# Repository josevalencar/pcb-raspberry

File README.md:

# Projeto de Placa de Circuito Impresso com Raspberry Pi Pico W - José Vitor Alencar

## Descrição
Este repositório contém os arquivos e recursos necessários para a construção de uma placa de circuito impresso (PCB) projetada para acoplar um Raspberry Pi Pico W. A placa inclui um dispositivo de acionamento de potência (transistor neste caso), um dispositivo sinalizador (LED neste caso) e um dispositivo de entrada (analógico ou digital). 

## Componentes
- **Raspberry Pi Pico W:** Responsável pelo controle e processamento.
- **Transistor:** Utilizado para o acionamento de cargas ou dispositivos externos.
- **LED:** Serve como dispositivo de sinalização para o usuário.

## Estrutura do Repositório

```
/
├── circuito
│   ├── circuito-backups
│   ├── gerber-files # Arquivos gerber para fabricação
│   └── circuito.kicad # Arquivos kicad do circuito
├── src
│   └── teste.py  # Script principal para testar a pcb com o Raspberry Pi Pico W
└── README.md
```

## Imagens
### Esquemático no KiCad

*Figura 1: Esquemático do projeto desenvolvido no KiCad.*

### Editor de PCI no KiCad

*Figura 2: Layout da placa no editor de PCI do KiCad.*

### Visualizador 3D no KiCad

*Figura 3: Layout da placa com visualização 3D.*

## Como Usar
O diretório `circuito` contém os arquivos para o kicad. O diretório `src` tem um arquivo teste em python.

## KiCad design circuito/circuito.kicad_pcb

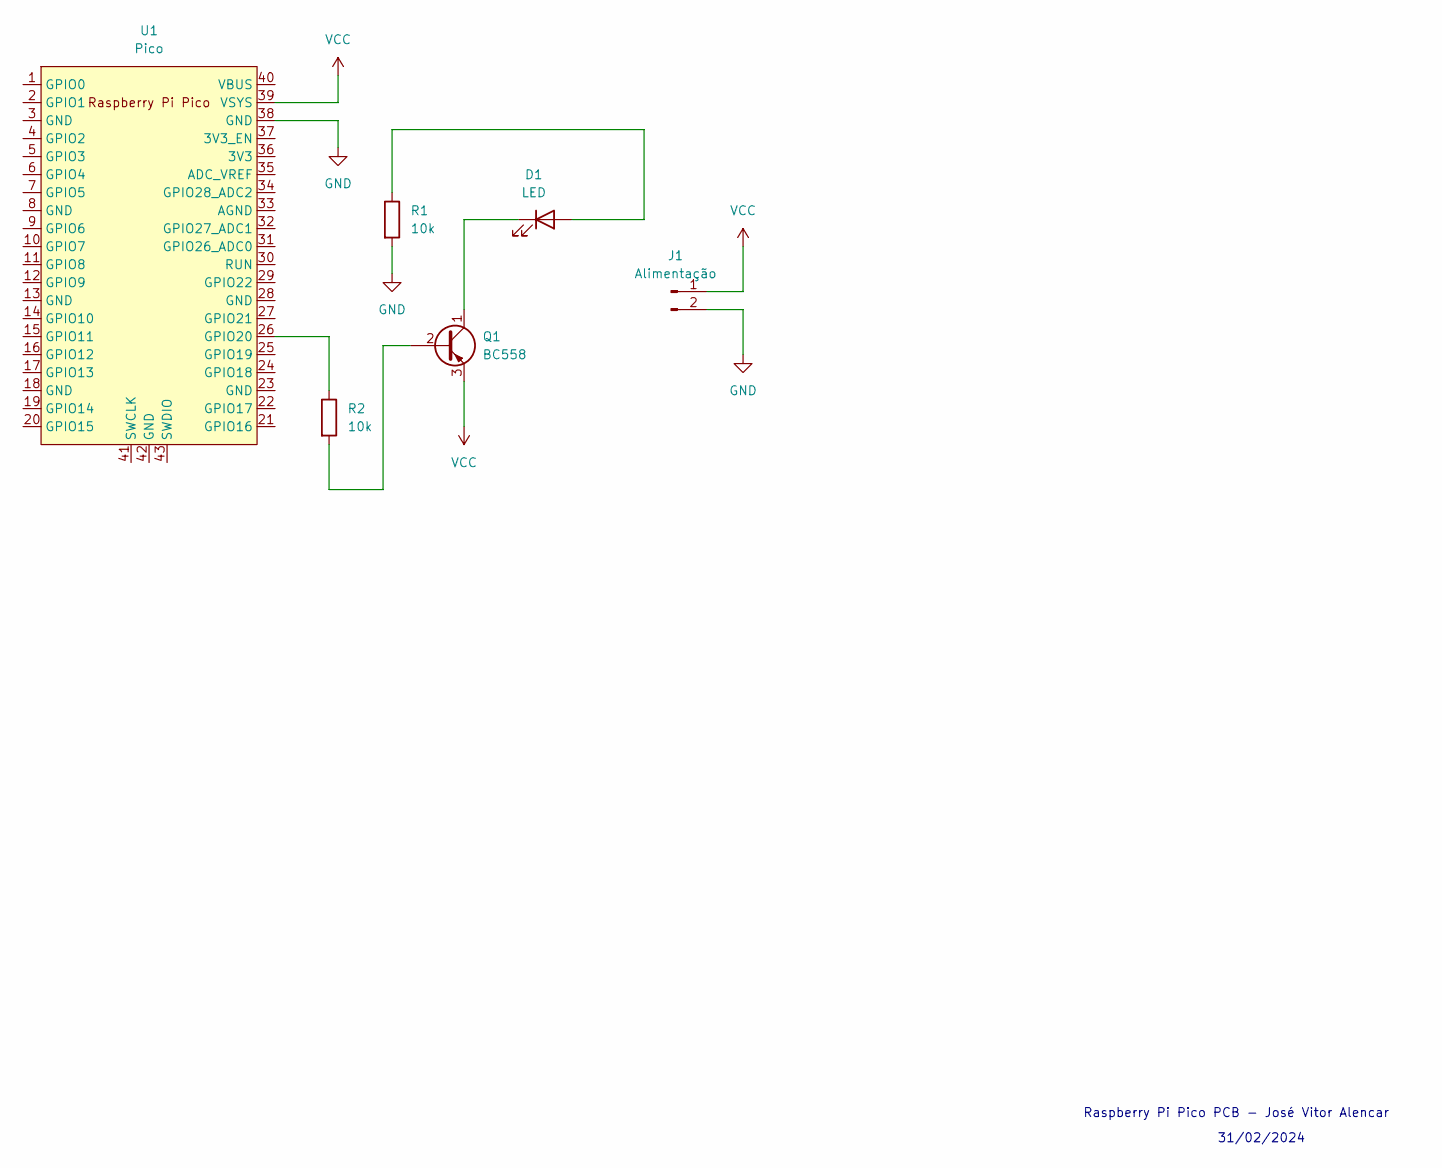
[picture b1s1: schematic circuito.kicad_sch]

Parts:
D1: LED; LED_0201_0603Metric
J1: Alimentação; AMASS_XT30PW-F_1x02_P2.50mm_Horizontal
Q1: BC558; TO-92_Inline
R1, R2: 10k; R_LDR_4.9x4.2mm_P2.54mm_Vertical
U1: Pico; RPi_Pico_SMD_TH

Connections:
GND: J1.2, R1.2, U1.38 (GND)
unnamed: D1.2 (A), R1.1
unnamed: D1.1 (K), Q1.1 (C)
unnamed: Q1.2 (B), R2.2
unnamed: R2.1, U1.26 (GPIO20)
VCC: J1.1, Q1.3 (E), U1.39 (VSYS)

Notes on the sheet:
31/02/2024
Raspberry Pi Pico PCB - José Vitor Alencar

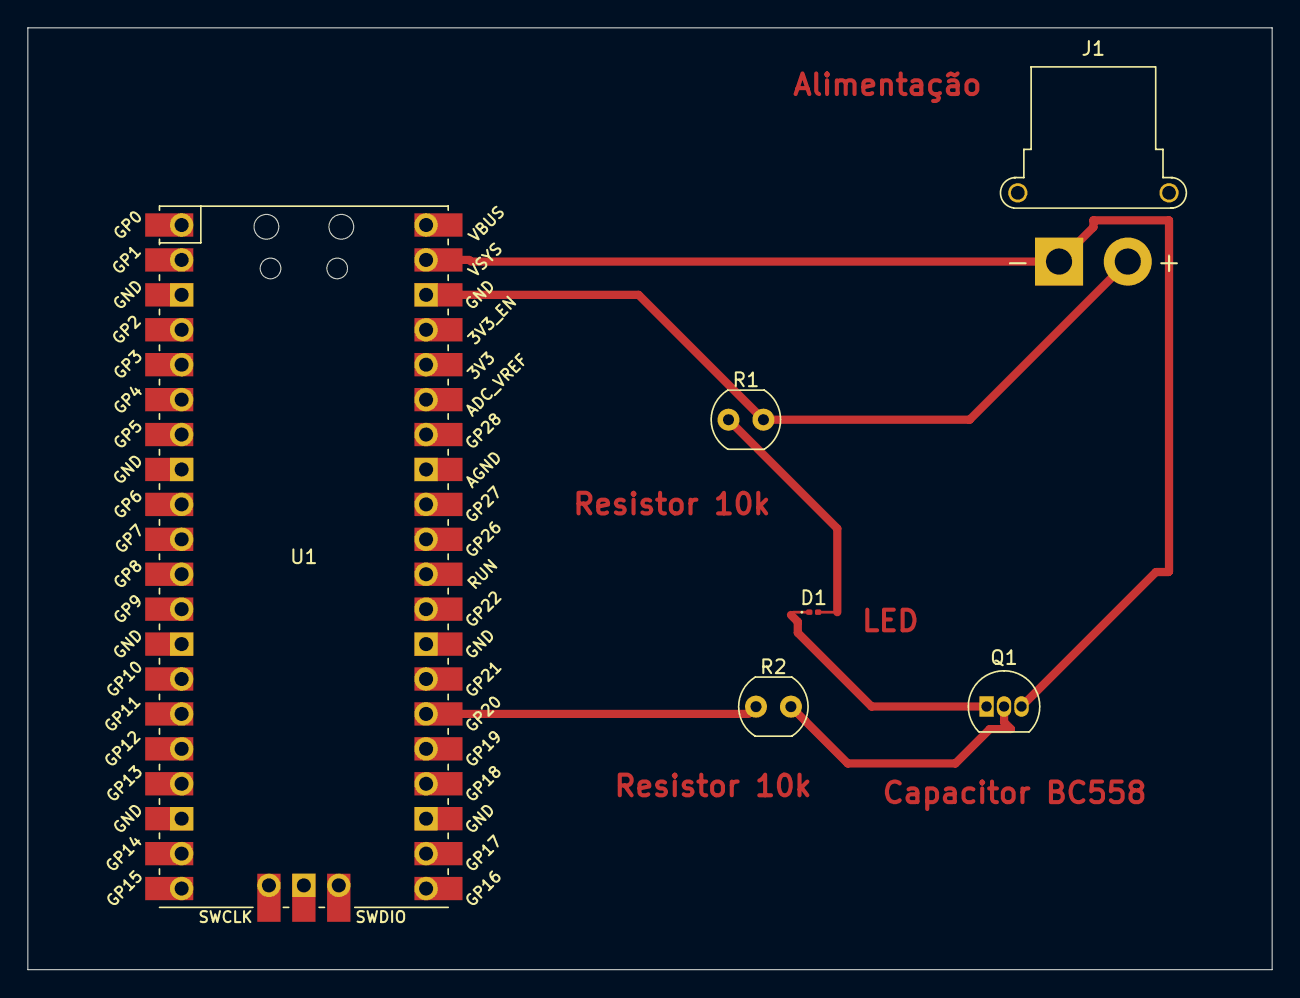
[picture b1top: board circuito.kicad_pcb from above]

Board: 2 copper layers, 90.5 x 68.5 mm, 6 parts (0 on the bottom side), 6 nets.

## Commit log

2024-04-01 feat todas alterações
2024-04-01 correções do readme
2024-04-01 feat introdução das linhas na pcb e visualizador 3D
